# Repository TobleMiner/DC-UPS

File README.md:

DC uninterruptible power supply
===============================

This repository contains the design files for a DC uninterruptible power
supply well suited to run network appliances like small switches, home
routes and WLAN access points.

**I would not recommend ordering RevC yet as it is still untested.**  
**I would not recommend ordering RevB yet as there are still some issues with the current design.
See [Rev B issues](https://github.com/TobleMiner/DC-UPS#rev-b-issues) below.**

# Features

 - 3 DC outputs
 - Selectable output voltage (9V/12V/12.5V/15V)
 - USB-C power output (5V only, 3A)
 - Builtin, easy to replace batteries (2x Li-Ion 18650)
 - Builtin Prometheus-exporter with comprehensive metrics
 - Open Source firmware (ESP32-based, esp-idf framework)
 - Easy software updates via back USB port

# Construction

The mechanical construction of the DC UPS is based on 4 assemblies:
 - Hammond Manufacturing 1455L1201BK aluminum case
 - Main PCB
 - Aluminum core PCB front panel
 - Aluminum core PCB rear panel

The three PCBs have been optimized for manufacturing through JLCPCB.  
The main PCB is also designed to be suitable for assembly through JLCPCB.  

The relevant fabrication files are located in `fab`.  

For final assembly it is recommended to countersink the screw holes in
front and rear panel. This will allow the screws included with the case to
sit flush.

## Main PCB assembly

When using the JLCPCB assembly service only a very limited number of
components needs to be assembled by hand:
 - Battery holder B1
 - OLED display U17

## Thermals

For better thermal management I would highly recommend to install a thick,
generously sized thermal pad below U4 and L2 contacting the bottom case if
using the UPS DC outputs beyond 40W output power.

# Firmware

The DC UPS is running Open Source firmware. Firmware source can be found on
GitHub here: [https://github.com/TobleMiner/dc-ups-firmware](https://github.com/TobleMiner/dc-ups-firmware)

# Why?

For a long time I was running the core of my home network (a cable modem,
router and switch) off a normal line-interactive AC UPS.  
This was never ideal for a number of reasons. First of all the UPS was
using sealed lead acid batterys. The UPS did not seem to treat those too
kindly and ended up degrading them beyond the point of useful capacity
within 2 - 5 years, depending on quality of the battery.  
Also I noticed that the UPS was always getting somewhat warm, suggesting
high idle power consumption. In this particular setup the core network
components only use about 12W. The AC UPS alone already used 10W while
idle. Quite the waste of power.  
Another worrying factor was overall system reliability. With the AC UPS
there were three seperate wall warts in use, each powering a single
device. Powering all network compoenents with DC directly this is down
to just one wall wart at the power input of the UPS itself.  
Additionally I was never quite happy with the monitoring options offered
by the AC UPS. While it was equipped with a USB port for monitoring the
available metrics were minimal. The DC UPS offers an Ethernet port and
hosts a Prometheus exporter offering all kinds of metrics relating to
power input and output, temperatures, battery health and battery
management internals.  
Finally the DC UPS is a lot smaller than available AC UPS options. The
following picture shows a comparison between the AC UPS I have been using
before and the DC UPS:  

# Rev B issues

Rev B is still more of a prototype than I'd like.
This is the list of currently know issues:
 - DCDC U4 startup is too slow on power failure, remove Q13
 - R47 and R48 are too high resistance for effective testing

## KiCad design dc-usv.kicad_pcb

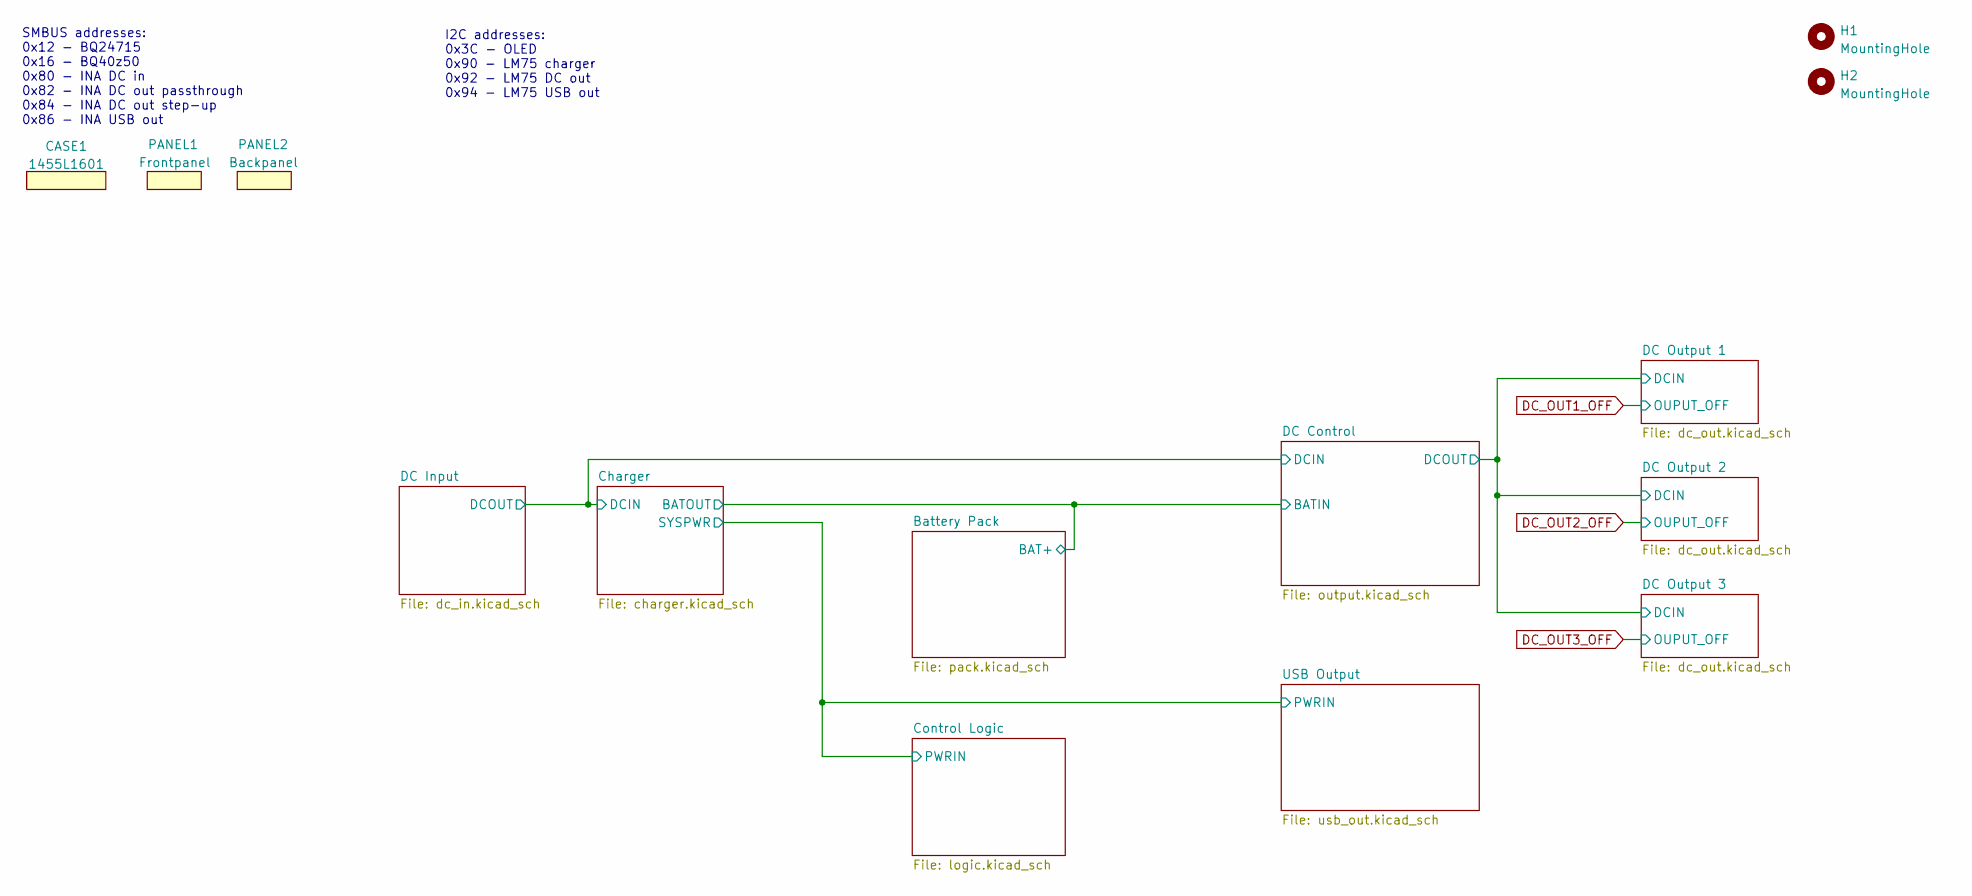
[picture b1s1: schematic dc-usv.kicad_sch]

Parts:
CASE1: 1455L1601
H1, H2: MountingHole; ToolingHole_JLCSMT
PANEL1: Frontpanel
PANEL2: Backpanel

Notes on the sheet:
I2C addresses: 0x3C - OLED 0x90 - LM75 charger 0x92 - LM75 DC out 0x94 - LM75 USB out
SMBUS addresses: 0x12 - BQ24715 0x16 - BQ40z50 0x80 - INA DC in 0x82 - INA DC out passthrough 0x84 - INA DC out step-up 0x86 - INA USB out

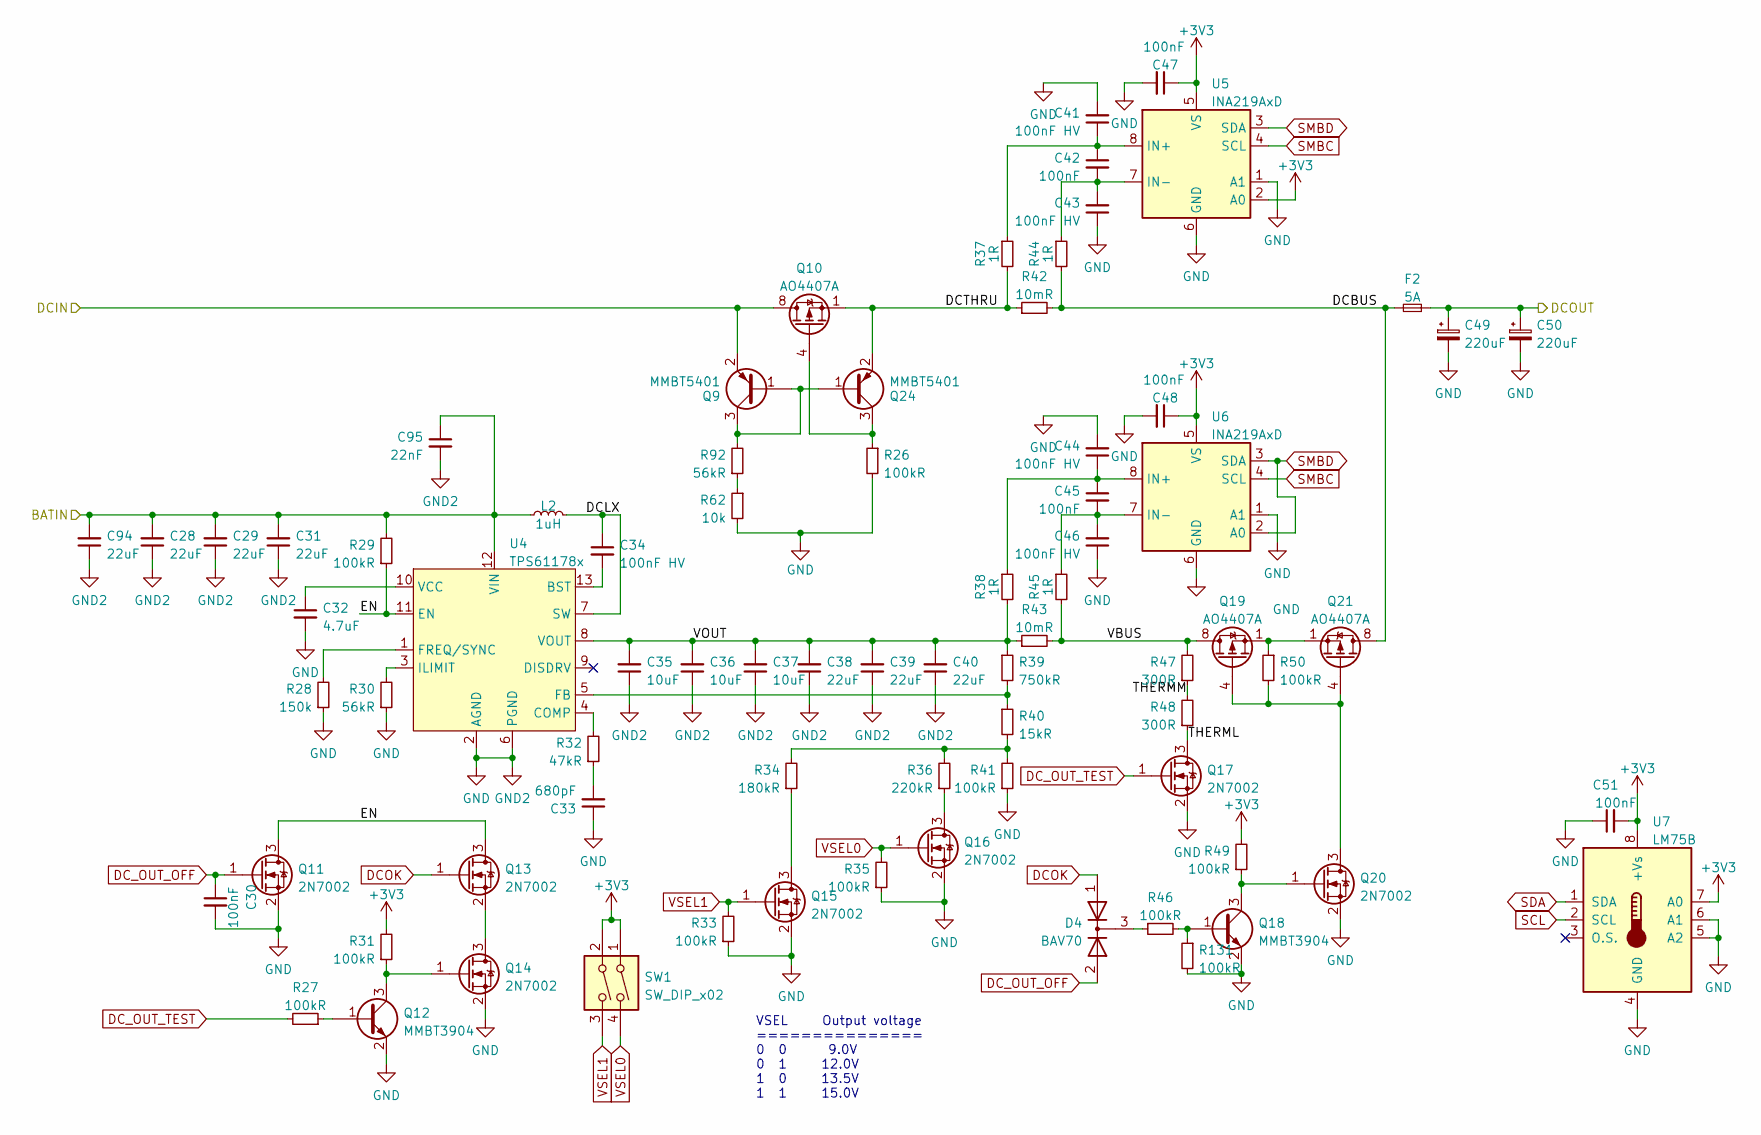
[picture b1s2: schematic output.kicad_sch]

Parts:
C28, C29, C31, C38, C39, C40, C94: 22uF; C_0805_2012Metric; LCSC C602037
C30, C42, C45, C47, C48, C51: 100nF; C_0402_1005Metric; LCSC C1525
C32: 4.7uF; C_0402_1005Metric; LCSC C23733
C33: 680pF; C_0603_1608Metric; LCSC C1630
C34, C41, C43, C44, C46: 100nF HV; C_0603_1608Metric; LCSC C14663
C35, C36, C37: 10uF; C_0805_2012Metric; LCSC C15850
C49, C50: 220uF; CP_Elec_6.3x7.7; LCSC C340768
C95: 22nF; C_0402_1005Metric; LCSC C1532
D4: BAV70; SOT-23; LCSC C68978
F2: 5A; Fuse_1206_3216Metric; LCSC C377290
L2: 1uH; L_Bourns_SRP7028A_7.3x6.6mm; LCSC C439005
Q9, Q24: MMBT5401; SOT-23; LCSC C8326
Q10, Q19, Q21: AO4407A; SOIC-8_3.9x4.9mm_P1.27mm; LCSC C167517
Q11, Q13, Q14, Q15, Q16, Q17, Q20: 2N7002; SOT-23; LCSC C8545
Q12, Q18: MMBT3904; SOT-23; LCSC C20526
R26, R27, R29, R31, R33, R35, R41, R46, R49, R50, R131: 100kR; R_0402_1005Metric; LCSC C25741
R28: 150k; R_0402_1005Metric; LCSC C25755
R30, R92: 56kR; R_0402_1005Metric; LCSC C25796
R32: 47kR; R_0603_1608Metric; LCSC C25819
R34: 180kR; R_0603_1608Metric; LCSC C22827
R36: 220kR; R_0402_1005Metric; LCSC C25767
R37, R38, R44, R45: 1R; R_0402_1005Metric; LCSC C25086
R39: 750kR; R_0603_1608Metric; LCSC C23240
R40: 15kR; R_0402_1005Metric; LCSC C25756
R42, R43: 10mR; R_0805_2012Metric; LCSC C270927
R47, R48: 300R; R_1206_3216Metric; LCSC C17887
R62: 10k; R_0402_1005Metric; LCSC C25744
SW1: SW_DIP_x02; PinHeader_2x02_P2.54mm_Vertical; LCSC C692490
U4: TPS61178x; VSON-HR-13; LCSC C127918
U5, U6: INA219AxD; SOIC-8_3.9x4.9mm_P1.27mm; LCSC C138706
U7: LM75B; MSOP-8_3x3mm_P0.65mm; LCSC C2837470

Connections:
/Battery Pack/BAT+: C28.2, C29.2, C31.2, C94.2, C95.1, L2.1, R29.2, U4.12 (VIN); also elsewhere on the board
/Charger/DCIN: Q9.2 (E), Q10.5 (D), Q10.6 (D), Q10.7 (D), Q10.8 (D); also elsewhere on the board
/DC Control/DCBUS: F2.2, Q21.5 (D), Q21.6 (D), Q21.7 (D), Q21.8 (D), R42.2, R44.2
/DC Control/DCLX: C34.1, L2.2, U4.7 (SW)
/DC Control/DCOUT: C49.1, C50.1, F2.1; also elsewhere on the board
/DC Control/DCTHRU: Q10.1 (S), Q10.2 (S), Q10.3 (S), Q24.2 (E), R37.2, R42.1
/DC Control/EN: Q11.3 (D), Q13.3 (D), R29.1, U4.11 (EN)
/DC Control/THERML: Q17.3 (D), R48.1
/DC Control/THERMM: R47.1, R48.2
/DC Control/VBUS: Q19.5 (D), Q19.6 (D), Q19.7 (D), Q19.8 (D), R43.2, R45.2, R47.2
/DC Control/VOUT: C35.2, C36.2, C37.2, C38.2, C39.2, C40.2, R38.2, R39.1, R43.1, U4.8 (VOUT)
DCOK: D4.1 (A), Q13.1 (G); also elsewhere on the board
DC_OUT_OFF: C30.1, D4.2 (A), Q11.1 (G); also elsewhere on the board
DC_OUT_TEST: Q17.1 (G), R27.2; also elsewhere on the board
unnamed: C33.2, R32.1
unnamed: D4.3 (K), R46.1
unnamed: Q10.4 (G), Q24.3 (C), R26.1
unnamed: Q12.1 (B), R27.1
unnamed: Q12.3 (C), Q14.1 (G), R31.1
unnamed: Q13.2 (S), Q14.3 (D)
unnamed: Q15.3 (D), R34.1
unnamed: Q16.3 (D), R36.1
unnamed: Q18.1 (B), R46.2, R131.1
unnamed: Q18.3 (C), Q20.1 (G), R49.1
unnamed: Q19.4 (G), Q20.3 (D), Q21.4 (G), R50.2
unnamed: Q19.1 (S), Q19.2 (S), Q19.3 (S), Q21.1 (S), Q21.2 (S), Q21.3 (S), R50.1
unnamed: Q9.1 (B), Q9.3 (C), Q24.1 (B), R92.2
unnamed: R34.2, R36.2, R40.2, R41.2
unnamed: C34.2, U4.13 (BST)
unnamed: R32.2, U4.4 (COMP)
unnamed: R39.2, R40.1, U4.5 (FB)
unnamed: R28.2, U4.1 (FREQ/SYNC)
unnamed: R30.2, U4.3 (ILIMIT)
unnamed: C32.1, U4.10 (VCC)
unnamed: C41.1, C42.1, R37.1, U5.8 (IN+)
unnamed: C42.2, C43.2, R44.1, U5.7 (IN-)
unnamed: C44.1, C45.1, R38.1, U6.8 (IN+)
unnamed: C45.2, C46.2, R45.1, U6.7 (IN-)
SCL: U7.2 (SCL); also elsewhere on the board
SDA: U7.1 (SDA); also elsewhere on the board
SMBC: U5.4 (SCL), U6.4 (SCL); also elsewhere on the board
SMBD: U5.3 (SDA), U6.2 (A0), U6.3 (SDA); also elsewhere on the board
VSEL0: Q16.1 (G), R35.2, SW1.4; also elsewhere on the board
VSEL1: Q15.1 (G), R33.2, SW1.3; also elsewhere on the board

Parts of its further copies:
R93: 10k; R_0402_1005Metric; LCSC C25744

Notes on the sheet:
VSEL Output voltage =============== 0 0 9.0V 0 1 12.0V 1 0 13.5V 1 1 15.0V

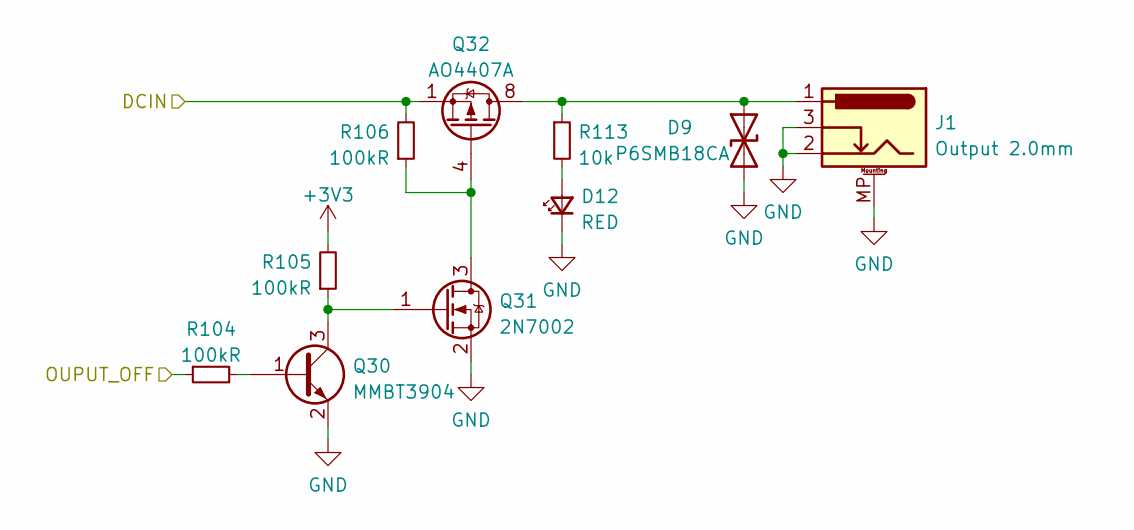
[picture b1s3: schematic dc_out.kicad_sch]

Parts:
D9: P6SMB18CA; D_SMB; LCSC C384916
D12: RED; LED_Indicator_RED_MHK1373CRBDT; LCSC C417352
J1: Output 2.0mm; BarrelJack_2.0mm_DC-044B; LCSC C397334
Q30: MMBT3904; SOT-23; LCSC C20526
Q31: 2N7002; SOT-23; LCSC C8545
Q32: AO4407A; SOIC-8_3.9x4.9mm_P1.27mm; LCSC C167517
R104, R105, R106: 100kR; R_0402_1005Metric; LCSC C25741
R113: 10k; R_0402_1005Metric; LCSC C25744

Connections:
/DC Control/DCOUT: Q32.1 (S), Q32.2 (S), Q32.3 (S), R106.2; also elsewhere on the board
DC_OUT1_OFF: R104.1; also elsewhere on the board
unnamed: D9.1 (A1), J1.1, Q32.5 (D), Q32.6 (D), Q32.7 (D), Q32.8 (D), R113.1
unnamed: D12.2 (A), R113.2
unnamed: Q30.1 (B), R104.2
unnamed: Q30.3 (C), Q31.1 (G), R105.1
unnamed: Q31.3 (D), Q32.4 (G), R106.1

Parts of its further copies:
D10, D11: P6SMB18CA; D_SMB; LCSC C384916
D13, D14: RED; LED_Indicator_RED_MHK1373CRBDT; LCSC C417352
J2, J3: Output 2.0mm; BarrelJack_2.0mm_DC-044B; LCSC C397334
Q33, Q36: MMBT3904; SOT-23; LCSC C20526
Q34, Q37: 2N7002; SOT-23; LCSC C8545
Q35, Q38: AO4407A; SOIC-8_3.9x4.9mm_P1.27mm; LCSC C167517
R107, R108, R109, R110, R111, R112: 100kR; R_0402_1005Metric; LCSC C25741
R114, R115: 10k; R_0402_1005Metric; LCSC C25744

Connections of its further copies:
/DC Control/DCOUT: Q35.1 (S), Q35.2 (S), Q35.3 (S), Q38.1 (S), Q38.2 (S), Q38.3 (S), R109.2, R112.2; also elsewhere on the board
DC_OUT2_OFF: R107.1; also elsewhere on the board
DC_OUT3_OFF: R110.1; also elsewhere on the board
unnamed: D10.1 (A1), J2.1, Q35.5 (D), Q35.6 (D), Q35.7 (D), Q35.8 (D), R114.1
unnamed: D11.1 (A1), J3.1, Q38.5 (D), Q38.6 (D), Q38.7 (D), Q38.8 (D), R115.1
unnamed: D13.2 (A), R114.2
unnamed: D14.2 (A), R115.2
unnamed: Q33.1 (B), R107.2
unnamed: Q33.3 (C), Q34.1 (G), R108.1
unnamed: Q34.3 (D), Q35.4 (G), R109.1
unnamed: Q36.1 (B), R110.2
unnamed: Q36.3 (C), Q37.1 (G), R111.1
unnamed: Q37.3 (D), Q38.4 (G), R112.1

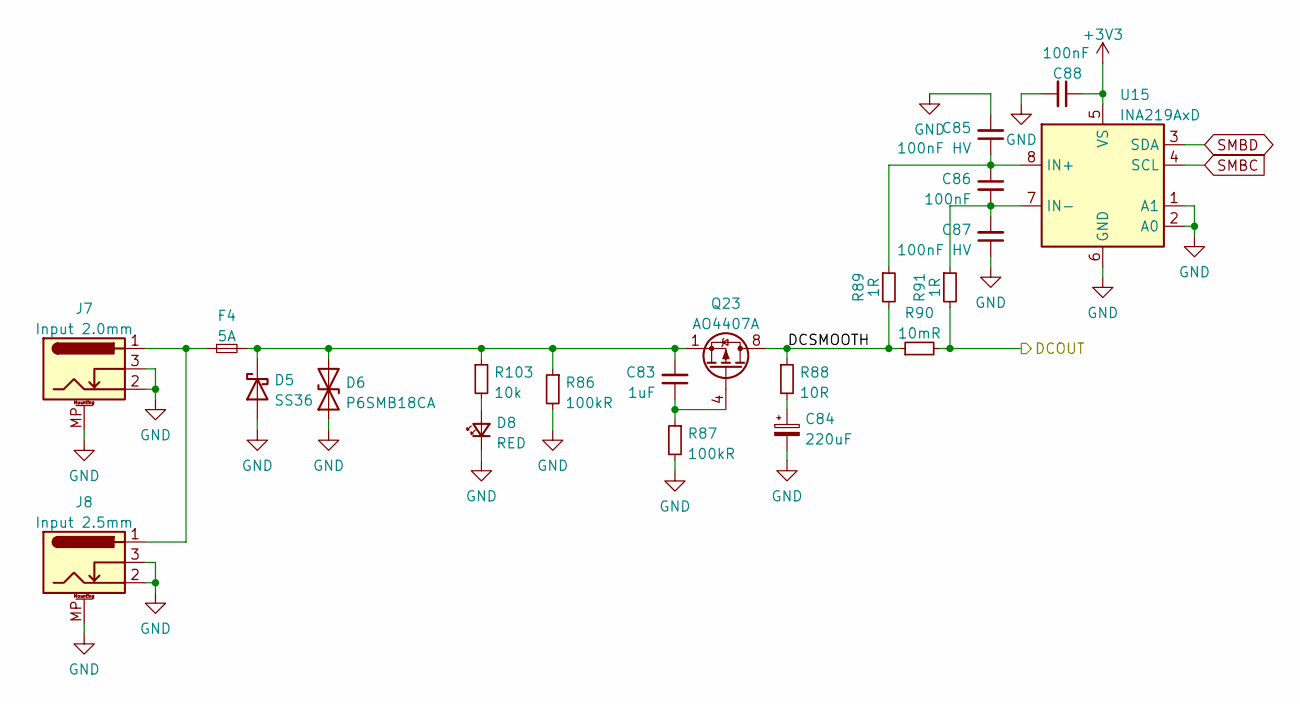
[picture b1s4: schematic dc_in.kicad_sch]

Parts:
C83: 1uF; C_0402_1005Metric; LCSC C52923
C84: 220uF; CP_Elec_6.3x7.7; LCSC C340768
C85, C87: 100nF HV; C_0603_1608Metric; LCSC C14663
C86, C88: 100nF; C_0402_1005Metric; LCSC C1525
D5: SS36; D_SMC; LCSC C35722
D6: P6SMB18CA; D_SMB; LCSC C384916
D8: RED; LED_Indicator_RED_MHK1373CRBDT; LCSC C417352
F4: 5A; Fuse_1206_3216Metric; LCSC C377290
J7: Input 2.0mm; BarrelJack_2.0mm_DC-044B; LCSC C397334
J8: Input 2.5mm; BarrelJack_2.5mm_DC-044K-D025; LCSC C963204
Q23: AO4407A; SOIC-8_3.9x4.9mm_P1.27mm; LCSC C167517
R86, R87: 100kR; R_0402_1005Metric; LCSC C25741
R88: 10R; R_1206_3216Metric; LCSC C17903
R89, R91: 1R; R_0402_1005Metric; LCSC C25086
R90: 10mR; R_0805_2012Metric; LCSC C270927
R103: 10k; R_0402_1005Metric; LCSC C25744
U15: INA219AxD; SOIC-8_3.9x4.9mm_P1.27mm; LCSC C138706

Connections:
/Charger/DCIN: R90.2, R91.2; also elsewhere on the board
/DC Input/DCSMOOTH: Q23.5 (D), Q23.6 (D), Q23.7 (D), Q23.8 (D), R88.1, R89.2, R90.1
unnamed: C84.1, R88.2
unnamed: C83.2, D5.1 (K), D6.2 (A2), F4.2, Q23.1 (S), Q23.2 (S), Q23.3 (S), R86.1, R103.1
unnamed: D8.2 (A), R103.2
unnamed: F4.1, J7.1, J8.1
unnamed: C83.1, Q23.4 (G), R87.1
unnamed: C85.1, C86.1, R89.1, U15.8 (IN+)
unnamed: C86.2, C87.2, R91.1, U15.7 (IN-)
SMBC: U15.4 (SCL); also elsewhere on the board
SMBD: U15.3 (SDA); also elsewhere on the board

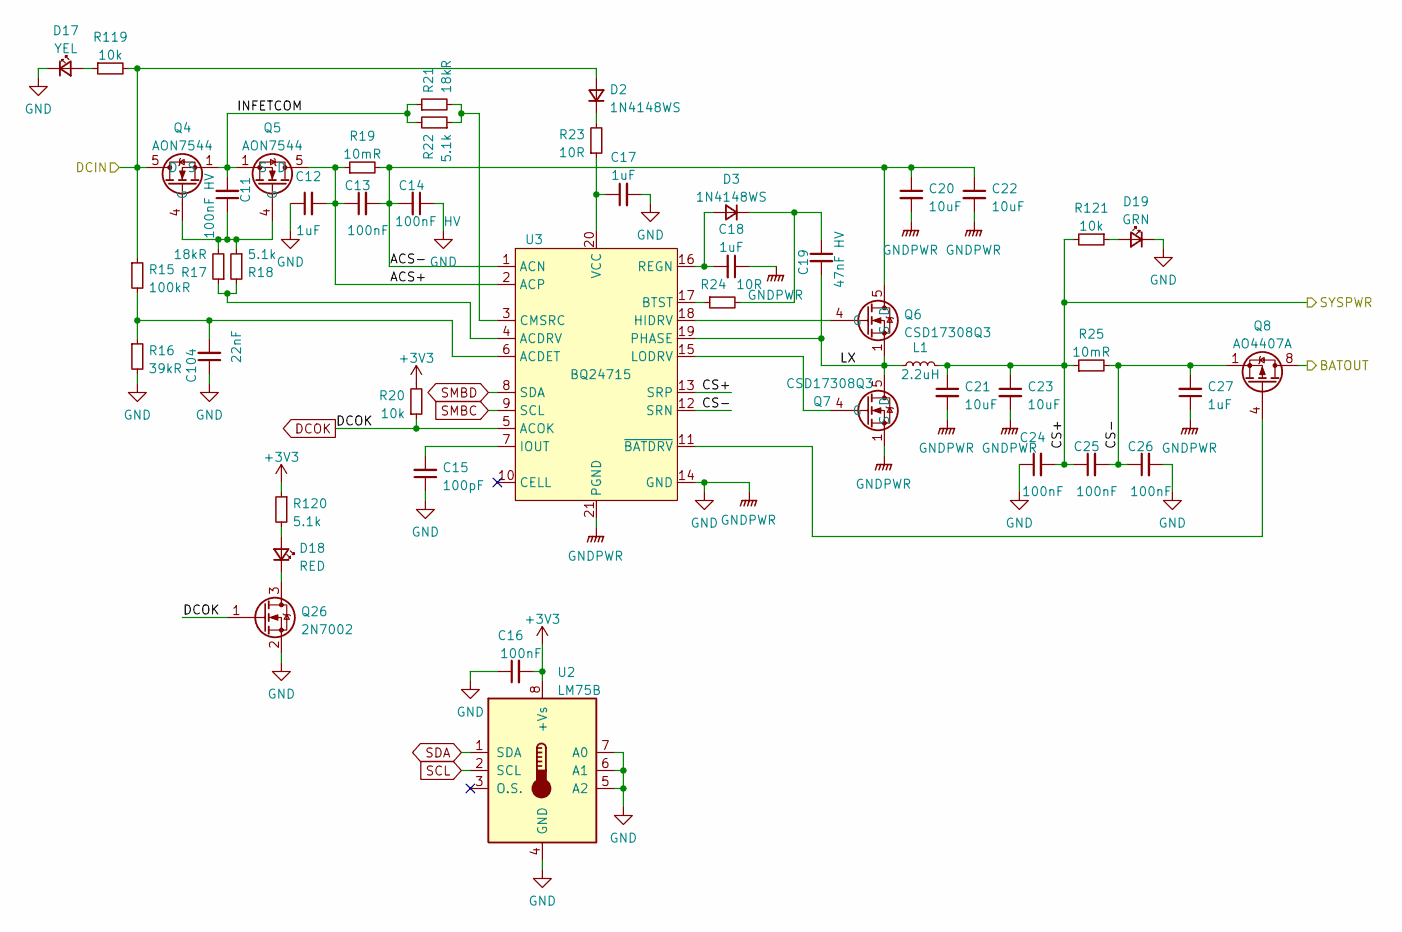
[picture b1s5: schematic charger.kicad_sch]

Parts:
C11, C14: 100nF HV; C_0603_1608Metric; LCSC C14663
C12, C17, C18, C27: 1uF; C_0402_1005Metric; LCSC C52923
C13, C16, C24, C25, C26: 100nF; C_0402_1005Metric; LCSC C1525
C15: 100pF; C_0402_1005Metric; LCSC C1546
C19: 47nF HV; C_0603_1608Metric; LCSC C1622
C20, C21, C22, C23: 10uF; C_0805_2012Metric; LCSC C15850
C104: 22nF; C_0402_1005Metric; LCSC C1532
D2, D3: 1N4148WS; D_SOD-323; LCSC C2128
D17: YEL; LED_0603_1608Metric; LCSC C72038
D18: RED; LED_0603_1608Metric; LCSC C2286
D19: GRN; LED_0603_1608Metric; LCSC C72043
L1: 2.2uH; L_Taiyo-Yuden_MD-4040; LCSC C98361
Q4, Q5: AON7544; DFN-8-FET_3x3mm_P0.65mm; LCSC C315567
Q6, Q7: CSD17308Q3; DFN-8-FET_3x3mm_P0.65mm; LCSC C294987
Q8: AO4407A; SOIC-8_3.9x4.9mm_P1.27mm; LCSC C167517
Q26: 2N7002; SOT-23; LCSC C8545
R15: 100kR; R_0402_1005Metric; LCSC C25741
R16: 39kR; R_0402_1005Metric; LCSC C25783
R17, R21: 18kR; R_0402_1005Metric; LCSC C25762
R18, R22, R120: 5.1k; R_0402_1005Metric; LCSC C25905
R19, R25: 10mR; R_0805_2012Metric; LCSC C270927
R20, R119, R121: 10k; R_0402_1005Metric; LCSC C25744
R23, R24: 10R; R_0402_1005Metric; LCSC C25077
U2: LM75B; MSOP-8_3x3mm_P0.65mm; LCSC C2837470
U3: BQ24715; QFN-20-1EP_3.5x3.5mm_P0.5mm_EP2x2mm_ThermalVias; LCSC C276341

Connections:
/Battery Pack/BAT+: Q8.5 (D), Q8.6 (D), Q8.7 (D), Q8.8 (D); also elsewhere on the board
/Charger/ACS+: C12.2, C13.1, Q5.5 (D), Q5.6 (D), Q5.7 (D), Q5.8 (D), Q5.9 (D), R19.1, U3.2 (ACP)
/Charger/ACS-: C13.2, C14.2, C20.1, C22.1, Q6.5 (D), Q6.6 (D), Q6.7 (D), Q6.8 (D), Q6.9 (D), R19.2, U3.1 (ACN)
/Charger/CS+: C21.1, C23.1, C24.2, C25.1, L1.2, R25.1, R121.2, U3.13 (SRP); also elsewhere on the board
/Charger/CS-: C25.2, C26.1, C27.2, Q8.1 (S), Q8.2 (S), Q8.3 (S), R25.2, U3.12 (SRN)
/Charger/DCIN: D2.2 (A), Q4.5 (D), Q4.6 (D), Q4.7 (D), Q4.8 (D), Q4.9 (D), R15.1, R119.2; also elsewhere on the board
/Charger/INFETCOM: C11.2, Q4.1 (S), Q4.2 (S), Q4.3 (S), Q5.1 (S), Q5.2 (S), Q5.3 (S), R21.1, R22.2
/Charger/LX: C19.2, L1.1, Q6.1 (S), Q6.2 (S), Q6.3 (S), Q7.5 (D), Q7.6 (D), Q7.7 (D), Q7.8 (D), Q7.9 (D), U3.19 (PHASE)
DCOK: Q26.1 (G), R20.1, U3.5 (ACOK); also elsewhere on the board
unnamed: D2.1 (K), R23.2
unnamed: C18.2, D3.2 (A), U3.16 (REGN)
unnamed: C19.1, D3.1 (K), R24.2
unnamed: D17.2 (A), R119.1
unnamed: D18.2 (A), R120.2
unnamed: D18.1 (K), Q26.3 (D)
unnamed: D19.2 (A), R121.1
unnamed: C11.1, Q4.4 (G), Q5.4 (G), R17.2, R18.1
unnamed: Q6.4 (G), U3.18 (HIDRV)
unnamed: Q7.4 (G), U3.15 (LODRV)
unnamed: Q8.4 (G), U3.11 (~BATDRV)
unnamed: C104.2, R15.2, R16.1, U3.6 (ACDET)
unnamed: R17.1, R18.2, U3.4 (ACDRV)
unnamed: R24.1, U3.17 (BTST)
unnamed: R21.2, R22.1, U3.3 (CMSRC)
unnamed: C15.2, U3.7 (IOUT)
unnamed: C17.1, R23.1, U3.20 (VCC)
SCL: U2.2 (SCL); also elsewhere on the board
SDA: U2.1 (SDA); also elsewhere on the board
SMBC: U3.9 (SCL); also elsewhere on the board
SMBD: U3.8 (SDA); also elsewhere on the board

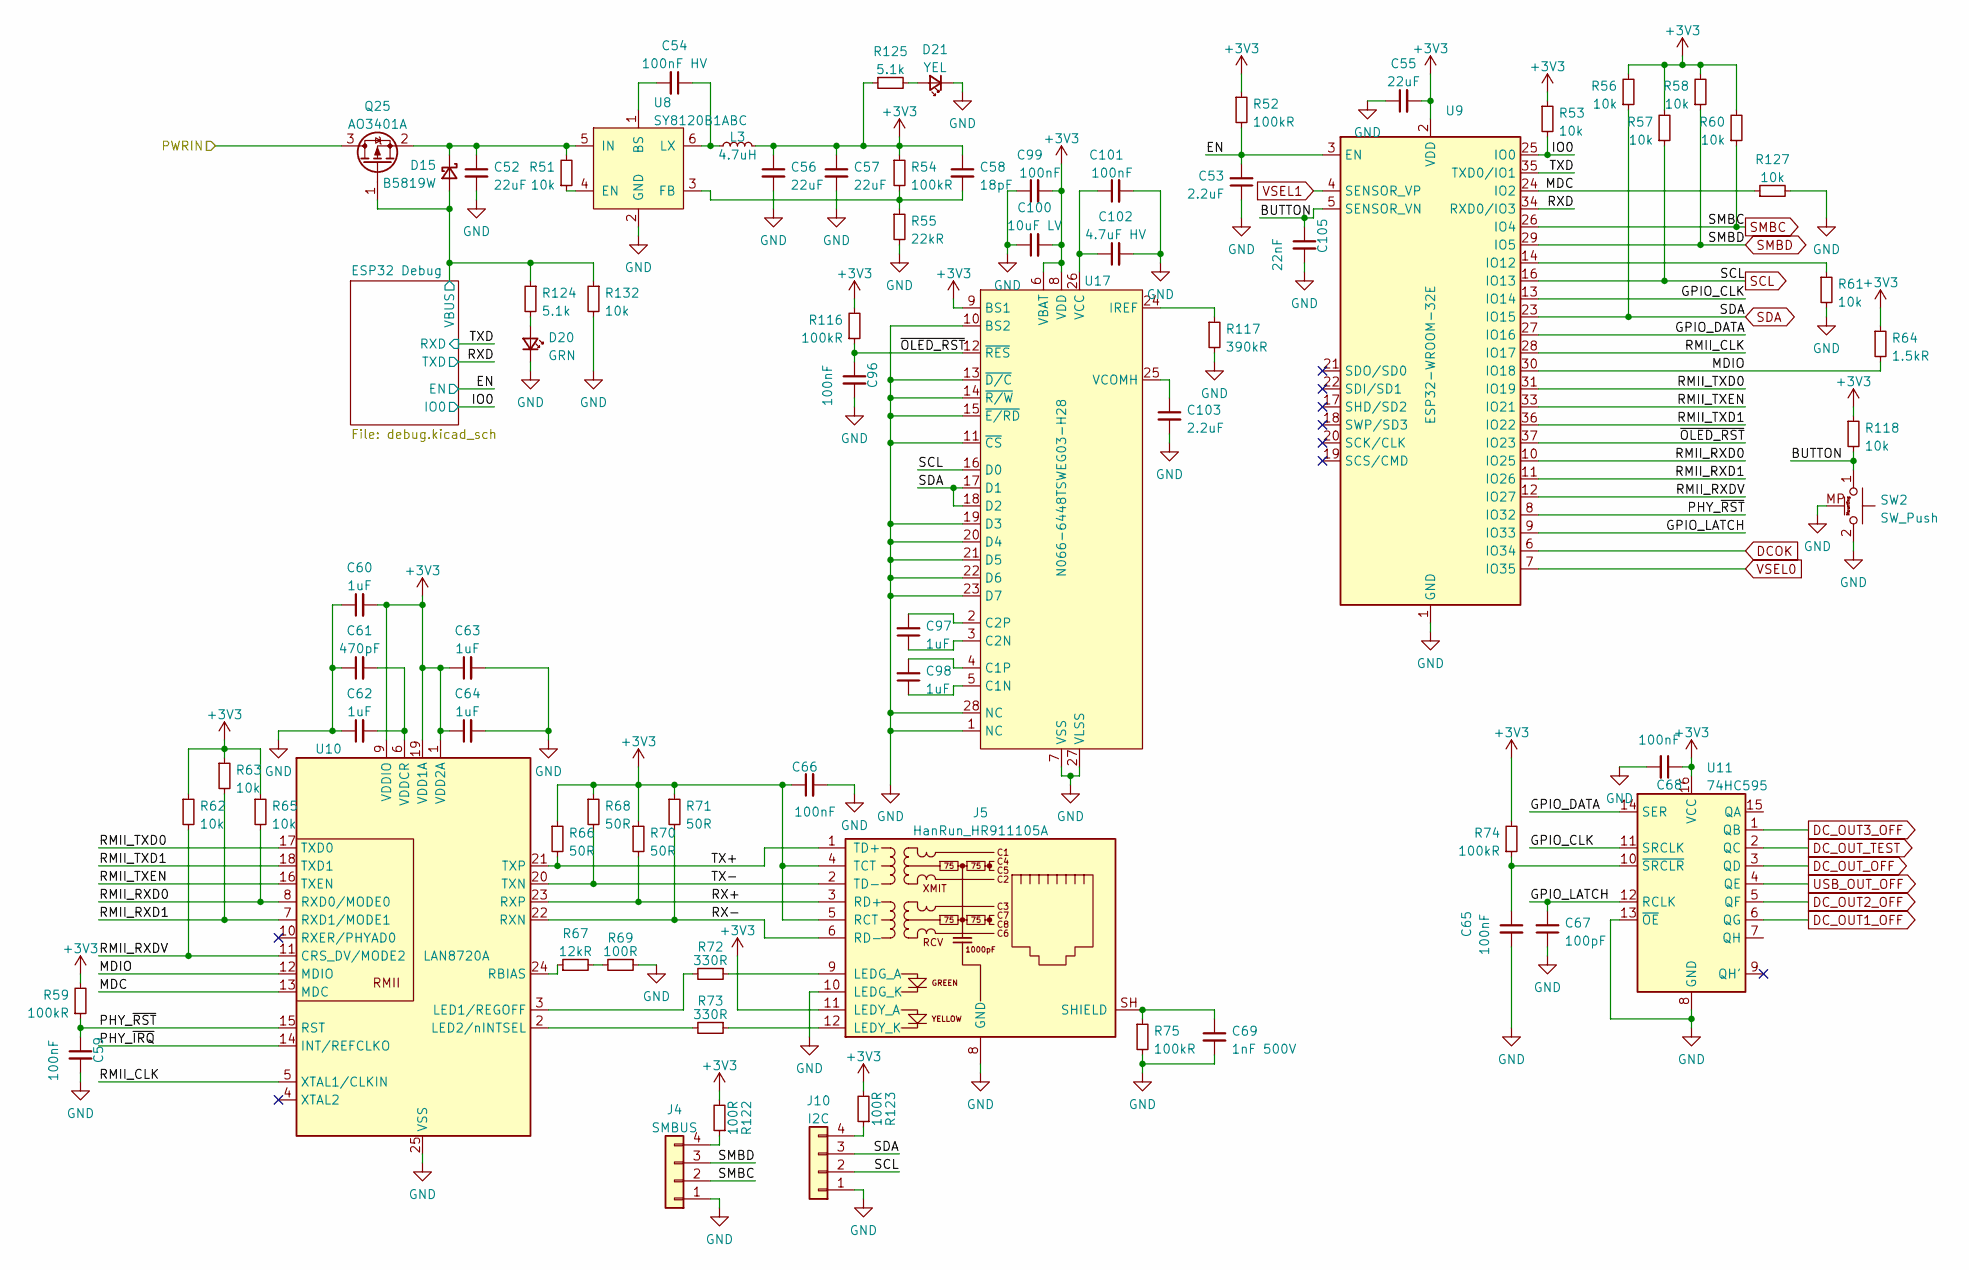
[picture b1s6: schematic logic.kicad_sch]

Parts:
C52, C55, C56, C57: 22uF; C_0805_2012Metric; LCSC C602037
C53, C103: 2.2uF; C_0603_1608Metric; LCSC C23630
C54: 100nF HV; C_0603_1608Metric; LCSC C14663
C58: 18pF; C_0402_1005Metric; LCSC C1549
C59, C65, C66, C68, C96, C99, C101: 100nF; C_0402_1005Metric; LCSC C1525
C60, C62, C63, C64, C97, C98: 1uF; C_0402_1005Metric; LCSC C52923
C61: 470pF; R_0402_1005Metric; LCSC C1537
C67: 100pF; C_0402_1005Metric; LCSC C1546
C69: 1nF 500V; C_1206_3216Metric; LCSC C35216
C100: 10uF LV; C_0402_1005Metric; LCSC C15525
C102: 4.7uF HV; C_0603_1608Metric; LCSC C19666
C105: 22nF; C_0402_1005Metric; LCSC C1532
D15: B5819W; D_SOD-123; LCSC C8598
D20: GRN; LED_0603_1608Metric; LCSC C72043
D21: YEL; LED_0603_1608Metric; LCSC C72038
J4: SMBUS; PinHeader_1x04_P2.54mm_Vertical
J5: HanRun_HR911105A; RJ45_Hanrun_HR911105A; LCSC C12074
J10: I2C; PinHeader_1x04_P2.54mm_Vertical
L3: 4.7uH; L_1008_2520Metric; LCSC C91237
Q25: AO3401A; SOT-23; LCSC C15127
R51, R53, R56, R57, R58, R60, R61, R62, R63, R65, R118, R127, R132: 10k; R_0402_1005Metric; LCSC C25744
R52, R54, R59, R74, R116: 100kR; R_0402_1005Metric; LCSC C25741
R55: 22kR; R_0402_1005Metric; LCSC C25768
R64: 1.5kR; R_0402_1005Metric; LCSC C25867
R66, R68, R70, R71: 50R; R_0402_1005Metric; LCSC C25120
R67: 12kR; R_0402_1005Metric; LCSC C25752
R69, R122, R123: 100R; R_0402_1005Metric; LCSC C25076
R72, R73: 330R; R_0402_1005Metric; LCSC C25104
R75: 100kR; R_1206_3216Metric; LCSC C17900
R117: 390kR; R_0603_1608Metric; LCSC C23150
R124, R125: 5.1k; R_0402_1005Metric; LCSC C25905
SW2: SW_Push; x-1825027-x; LCSC C266183
U8: SY8120B1ABC; SOT-23-6; LCSC C88474
U9: ESP32-WROOM-32E; ESP32-WROOM-32; LCSC C701342
U10: LAN8720A; QFN-24-1EP_4x4mm_P0.5mm_EP2.6x2.6mm; LCSC C45223
U11: 74HC595; SOIC-16_3.9x9.9mm_P1.27mm; LCSC C5947
U17: N066-6448TSWEG03-H28; LCSC C2890608

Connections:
/Charger/CS+: Q25.3 (D); also elsewhere on the board
/Control Logic/BUTTON: C105.1, R118.2, SW2.1, U9.5 (SENSOR_VN)
/Control Logic/EN: C53.2, R52.2, U9.3 (EN); also elsewhere on the board
/Control Logic/GPIO_CLK: U9.13 (IO14), U11.11 (SRCLK)
/Control Logic/GPIO_DATA: U9.27 (IO16), U11.14 (SER)
/Control Logic/GPIO_LATCH: C67.2, U9.9 (IO33), U11.12 (RCLK)
/Control Logic/IO0: R53.2, U9.25 (IO0); also elsewhere on the board
/Control Logic/MDC: R127.1, U9.24 (IO2), U10.13 (MDC)
/Control Logic/MDIO: R64.2, U9.30 (IO18), U10.12 (MDIO)
/Control Logic/PHY_~IRQ: U10.14 (INT/REFCLKO)
/Control Logic/PHY_~RST: C59.1, R59.1, U9.8 (IO32), U10.15 (RST)
/Control Logic/RMII_CLK: U9.28 (IO17), U10.5 (XTAL1/CLKIN)
/Control Logic/RMII_RXD0: R65.2, U9.10 (IO25), U10.8 (RXD0/MODE0)
/Control Logic/RMII_RXD1: R63.2, U9.11 (IO26), U10.7 (RXD1/MODE1)
/Control Logic/RMII_TXD0: U9.31 (IO19), U10.17 (TXD0)
/Control Logic/RMII_TXD1: U9.36 (IO22), U10.18 (TXD1)
/Control Logic/RMII_TXEN: U9.33 (IO21), U10.16 (TXEN)
/Control Logic/RX+: J5.3 (RD+), R70.2, U10.23 (RXP)
/Control Logic/RX-: J5.6 (RD-), R71.2, U10.22 (RXN)
/Control Logic/RXD: U9.34 (RXD0/IO3); also elsewhere on the board
/Control Logic/TX+: J5.1 (TD+), R66.2, U10.21 (TXP)
/Control Logic/TX-: J5.2 (TD-), R68.2, U10.20 (TXN)
/Control Logic/TXD: U9.35 (TXD0/IO1); also elsewhere on the board
/Control Logic/~OLED_RST: C96.1, R116.1, U9.37 (IO23), U17.12 (~RES)
DCOK: U9.6 (IO34); also elsewhere on the board
DC_OUT1_OFF: U11.6 (QG); also elsewhere on the board
DC_OUT2_OFF: U11.5 (QF); also elsewhere on the board
DC_OUT3_OFF: U11.1 (QB); also elsewhere on the board
DC_OUT_OFF: U11.3 (QD); also elsewhere on the board
DC_OUT_TEST: U11.2 (QC); also elsewhere on the board
unnamed: C52.1, D15.1 (K), Q25.2 (S), R51.2, U8.5 (IN)
unnamed: D20.2 (A), R124.2
unnamed: D21.2 (A), R125.2
unnamed: J4.4, R122.1
unnamed: J5.9 (LEDG_A), R72.1
unnamed: J5.12 (LEDY_K), R73.1
unnamed: C69.1, J5.SH (SHIELD), R75.1
unnamed: J10.4, R123.1
unnamed: R67.2, R69.2
unnamed: C54.2, U8.1 (BS)
unnamed: R51.1, U8.4 (EN)
unnamed: C58.2, R54.2, R55.1, U8.3 (FB)
unnamed: C54.1, L3.1, U8.6 (LX)
unnamed: R61.1, U9.14 (IO12)
unnamed: R72.2, U10.3 (LED1/REGOFF)
unnamed: R73.2, U10.2 (LED2/nINTSEL)
unnamed: R67.1, U10.24 (RBIAS)
unnamed: C61.2, C62.2, U10.6 (VDDCR)
unnamed: C65.1, R74.1, U11.10 (~SRCLR)
unnamed: C98.1, U17.5 (C1N)
unnamed: C98.2, U17.4 (C1P)
unnamed: C97.1, U17.3 (C2N)
unnamed: C97.2, U17.2 (C2P)
unnamed: R117.1, U17.24 (IREF)
unnamed: C101.1, C102.1, U17.26 (VCC)
unnamed: C103.1, U17.25 (VCOMH)
SCL: J10.2, R57.1, U9.16 (IO13), U17.16 (D0); also elsewhere on the board
SDA: J10.3, R56.1, U9.23 (IO15), U17.17 (D1), U17.18 (D2); also elsewhere on the board
SMBC: J4.2, R60.1, U9.26 (IO4); also elsewhere on the board
SMBD: J4.3, R58.1, U9.29 (IO5); also elsewhere on the board
USB_OUT_OFF: U11.4 (QE); also elsewhere on the board
VBUS: D15.2 (A), Q25.1 (G), R124.1, R132.1; also elsewhere on the board
VSEL0: U9.7 (IO35); also elsewhere on the board
VSEL1: U9.4 (SENSOR_VP); also elsewhere on the board

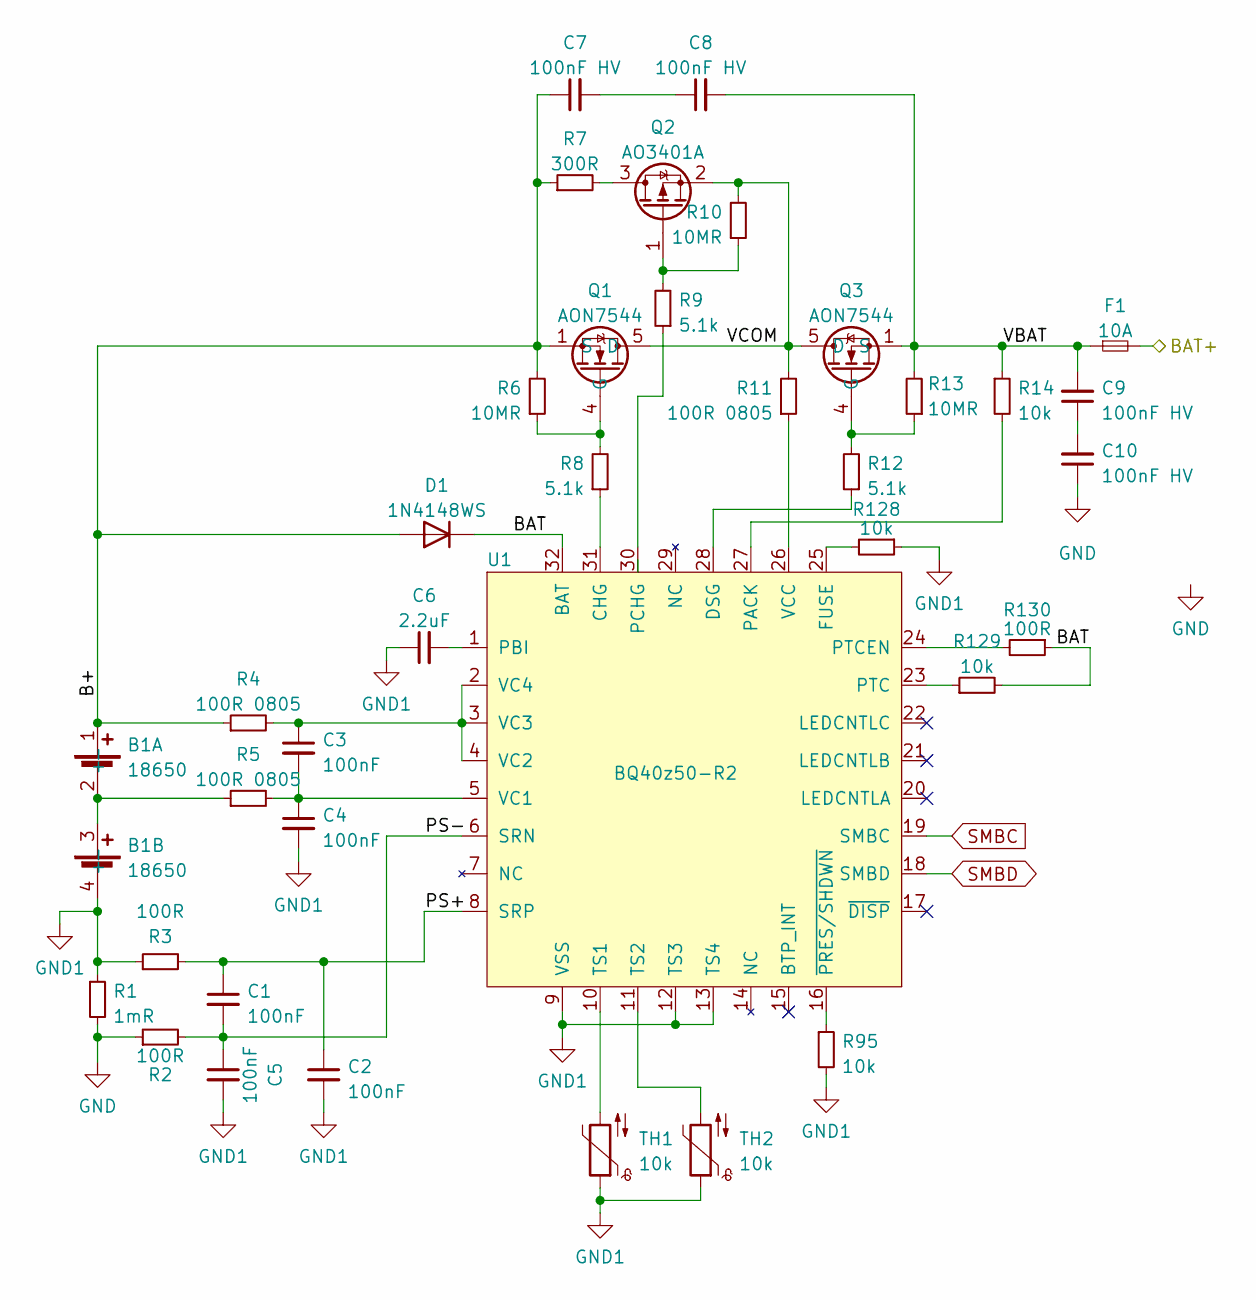
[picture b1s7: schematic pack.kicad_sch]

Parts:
B1: 18650; SMD-1048-dual-18650
C1, C2, C3, C4, C5: 100nF; C_0402_1005Metric; LCSC C1525
C6: 2.2uF; C_0603_1608Metric; LCSC C23630
C7, C8, C9, C10: 100nF HV; C_0603_1608Metric; LCSC C14663
D1: 1N4148WS; D_SOD-323; LCSC C2128
F1: 10A; Fuse_1206_3216Metric; LCSC C242475
Q1, Q3: AON7544; DFN-8-FET_3x3mm_P0.65mm; LCSC C315567
Q2: AO3401A; SOT-23; LCSC C15127
R1: 1mR; R_1206_3216Metric; LCSC C76287
R2, R3, R130: 100R; R_0402_1005Metric; LCSC C25076
R4, R5, R11: 100R 0805; R_0805_2012Metric; LCSC C17408
R6, R10, R13: 10MR; R_0402_1005Metric; LCSC C26082
R7: 300R; R_1206_3216Metric; LCSC C17887
R8, R9, R12: 5.1k; R_0402_1005Metric; LCSC C25905
R14, R95, R128, R129: 10k; R_0402_1005Metric; LCSC C25744
TH1, TH2: 10k; R_0402_1005Metric; LCSC C279801
U1: BQ40z50-R2; VQFN-32-4.1x4.1-EP-1.4; LCSC C179743

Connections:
/Battery Pack/B+: B1.1 (+), C7.1, D1.2 (A), Q1.1 (S), Q1.2 (S), Q1.3 (S), R4.1, R6.2, R7.1
/Battery Pack/BAT: D1.1 (K), R129.2, R130.1, U1.32 (BAT)
/Battery Pack/BAT+: F1.2; also elsewhere on the board
/Battery Pack/PS+: C1.1, C2.1, R3.2, U1.8 (SRP)
/Battery Pack/PS-: C1.2, C5.1, R2.2, U1.6 (SRN)
/Battery Pack/VBAT: C8.2, C9.2, F1.1, Q3.1 (S), Q3.2 (S), Q3.3 (S), R13.2, R14.1
/Battery Pack/VCOM: Q1.5 (D), Q1.6 (D), Q1.7 (D), Q1.8 (D), Q1.9 (D), Q2.2 (S), Q3.5 (D), Q3.6 (D), Q3.7 (D), Q3.8 (D), Q3.9 (D), R10.2, R11.2
GND1: B1.4 (-), C2.2, C4.2, C5.2, C6.1, R1.1, R3.1, R95.2, R128.1, TH1.1, TH2.1, U1.9 (VSS), U1.12 (TS3), U1.13 (TS4), U1.33 (PWRPD)
unnamed: B1.2 (-), B1.3 (+), R5.1
unnamed: C7.2, C8.1
unnamed: C9.1, C10.2
unnamed: Q1.4 (G), R6.1, R8.2
unnamed: Q2.3 (D), R7.2
unnamed: Q2.1 (G), R9.2, R10.1
unnamed: Q3.4 (G), R12.2, R13.1
unnamed: R8.1, U1.31 (CHG)
unnamed: R12.1, U1.28 (DSG)
unnamed: R128.2, U1.25 (FUSE)
unnamed: R14.2, U1.27 (PACK)
unnamed: C6.2, U1.1 (PBI)
unnamed: R9.1, U1.30 (PCHG)
unnamed: R129.1, U1.23 (PTC)
unnamed: R130.2, U1.24 (PTCEN)
unnamed: TH1.2, U1.10 (TS1)
unnamed: TH2.2, U1.11 (TS2)
unnamed: C3.2, C4.1, R5.2, U1.5 (VC1)
unnamed: C3.1, R4.2, U1.2 (VC4), U1.3 (VC3), U1.4 (VC2)
unnamed: R11.1, U1.26 (VCC)
unnamed: R95.1, U1.16 (~PRES/SHDWN)
SMBC: U1.19 (SMBC); also elsewhere on the board
SMBD: U1.18 (SMBD); also elsewhere on the board
